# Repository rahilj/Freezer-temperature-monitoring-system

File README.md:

# Freezer-temperature-monitoring-system
A low-cost, DIY temperature monitoring system for tracking temperature of fridge and freezers in a research lab setting. Setup consists of a central WiFi microcontroller (Particle.io P1/Photon) connected to TMP36 temperature sensor. The temperature data from sensor is logged periodically to free-to-use Google spreadsheet service. Users are notified by text/email when temperature deviates from set limits.

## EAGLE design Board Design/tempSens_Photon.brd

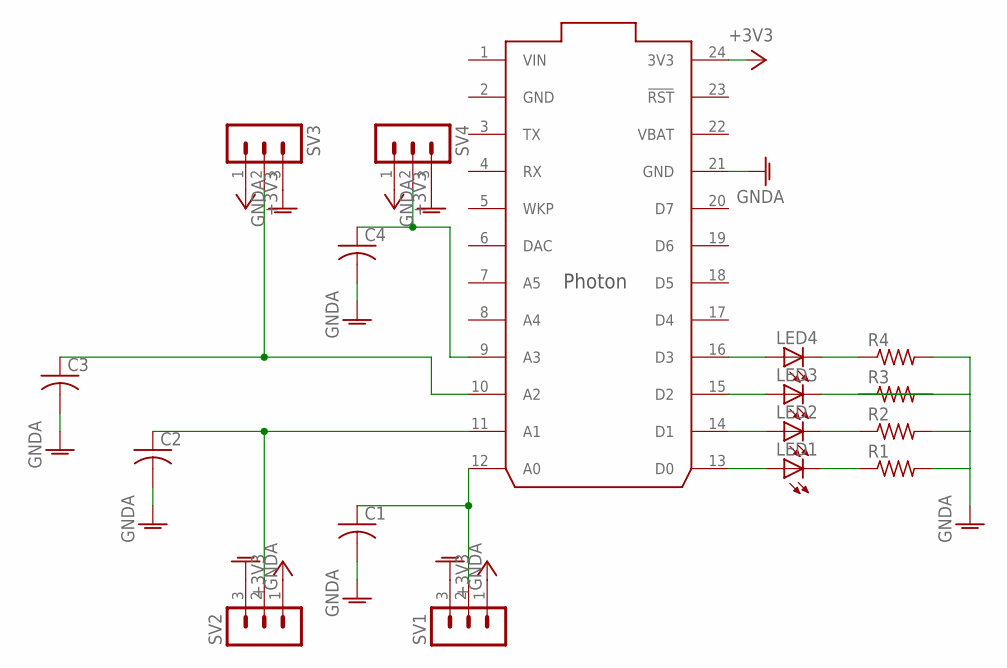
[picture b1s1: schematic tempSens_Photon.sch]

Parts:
C1, C2, C3, C4: C-USC0805; C0805
LED1, LED2, LED3, LED4: LEDCHIPLED_0805; CHIPLED_0805
R1, R2, R3, R4: R-US_R0805; R0805
SV1, SV2, SV3, SV4: CONN3PIN; MA03-1
U$1: PHOTON_SMD

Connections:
+3V3: SV1.1, SV2.1, SV3.1, SV4.1, U$1.24 (3V3)
GND: C1.2, C2.2, C3.2, C4.2, R1.2, R2.2, R3.1, R4.2, SV1.3, SV2.3, SV3.3, SV4.3, U$1.2 (GND), U$1.21 (GND)
unnamed: C1.1, SV1.2, U$1.12 (A0)
unnamed: C2.1, SV2.2, U$1.11 (A1)
unnamed: C3.1, SV3.2, U$1.10 (A2)
unnamed: C4.1, SV4.2, U$1.9 (A3)
unnamed: LED1.A, U$1.13 (D0)
unnamed: LED2.A, U$1.14 (D1)
unnamed: LED3.A, U$1.15 (D2)
unnamed: LED4.A, U$1.16 (D3)
unnamed: LED1.C, R1.1
unnamed: LED2.C, R2.1
unnamed: LED3.C, R3.2
unnamed: LED4.C, R4.1
VBAT: U$1.22 (VBAT)
VIN: U$1.1 (VIN)

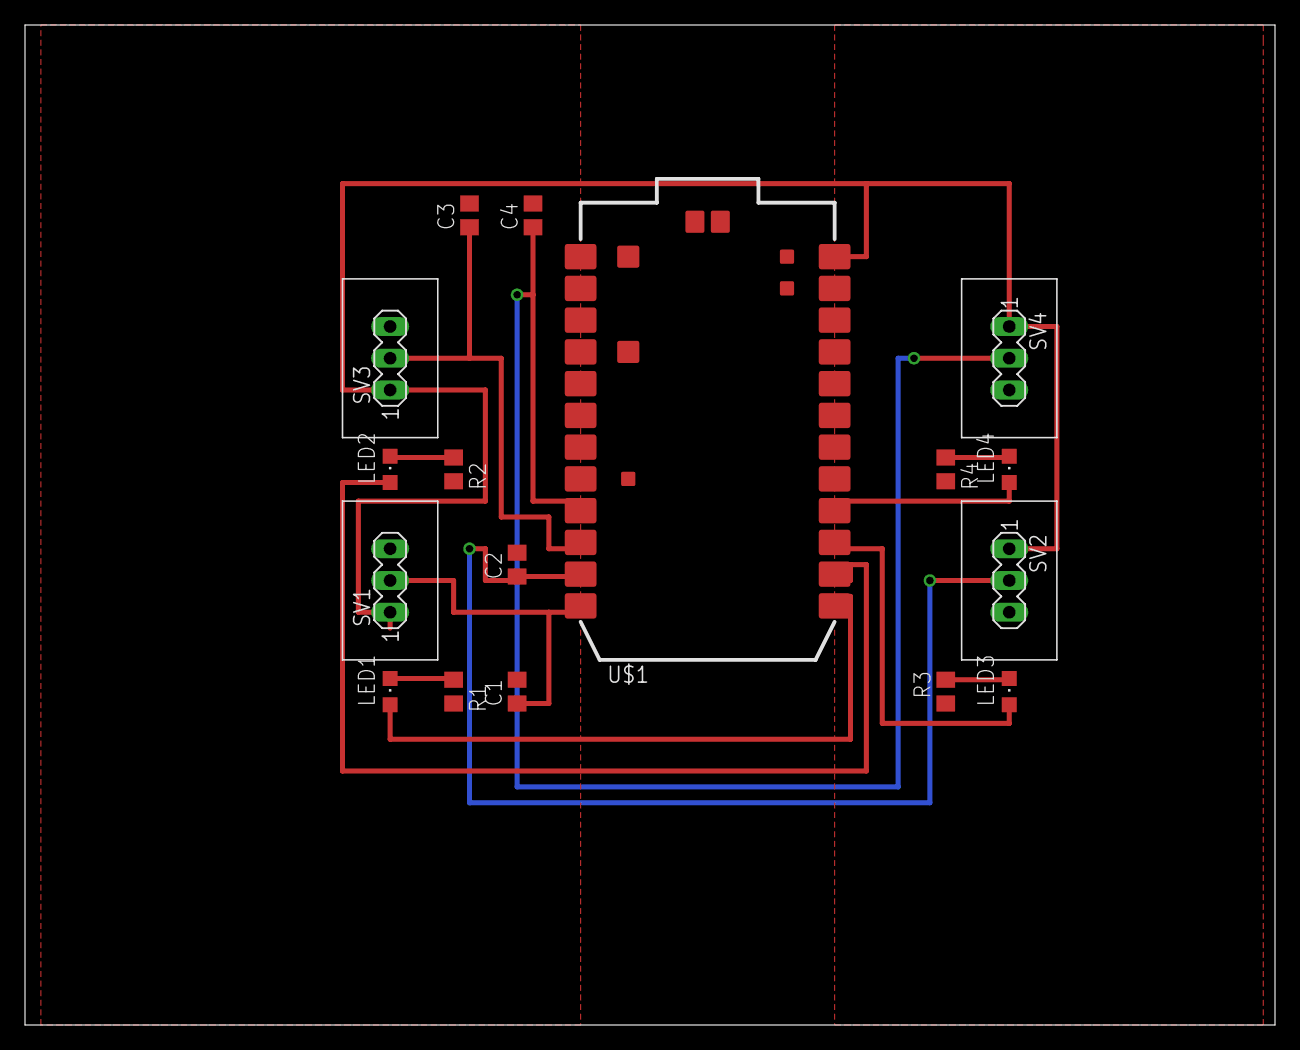
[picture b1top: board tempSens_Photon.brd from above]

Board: 2 copper layers, 100.0 x 80.0 mm, 17 parts (0 on the bottom side), 14 nets.

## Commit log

2016-01-20 Create firmware.ino
    Updated firmware with support for up to four temperature sensors.
2016-06-23 First Attempt at a EagleCAD PCB
    4 status LEDS
    Accomodates 4 sensors
2016-06-23 added git ignore
